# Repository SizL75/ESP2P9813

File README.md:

# ESP2P9813
PCB for ESP8266 ESP-01 board to control P9813 modules with 12v power supply

Can be used with fastled library, use the following settings:
```
#define DATA_PIN    2
#define CLK_PIN   0
#define LED_TYPE    P9813
#define COLOR_ORDER GRB
```

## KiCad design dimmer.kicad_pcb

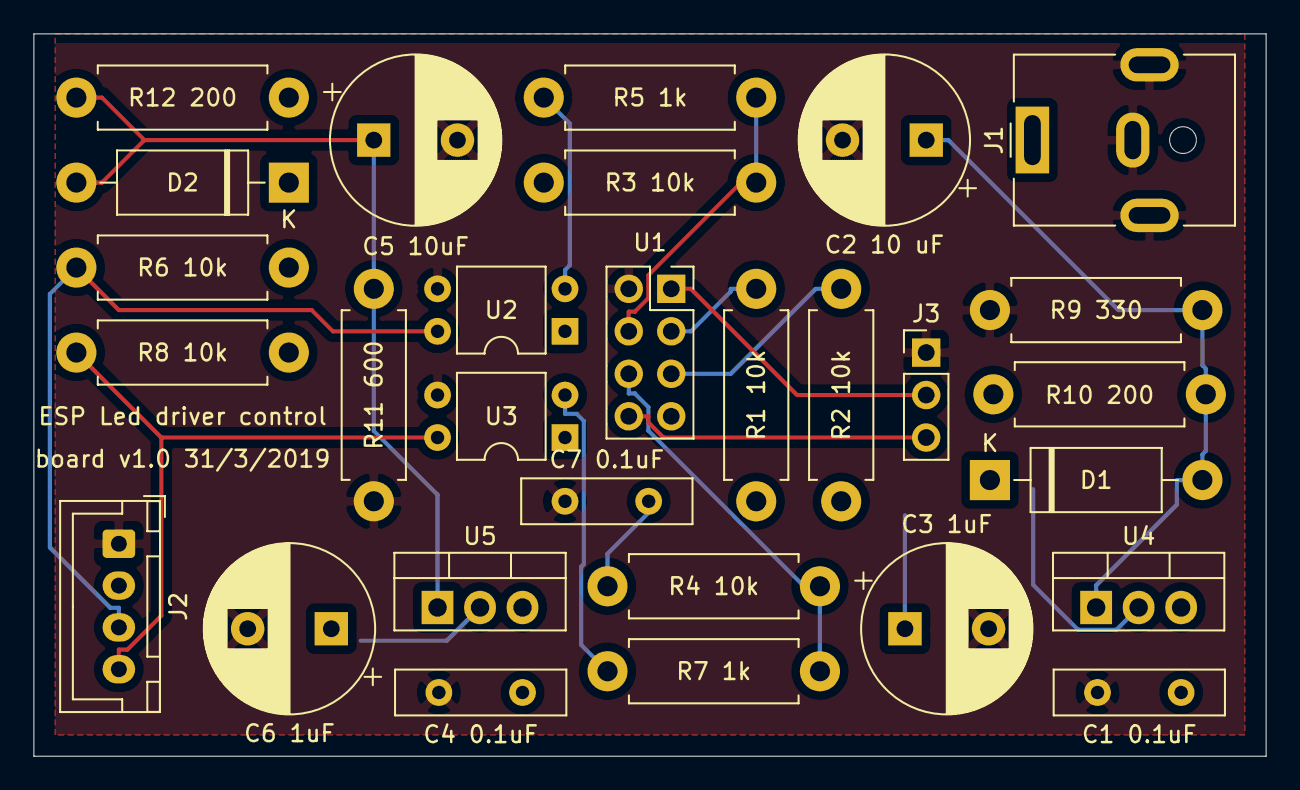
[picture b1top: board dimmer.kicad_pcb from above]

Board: 2 copper layers, 73.7 x 43.2 mm, 29 parts (0 on the bottom side), 16 nets.

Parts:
C1 0.1uF, C4 0.1uF, C7 0.1uF: 0.1uF; C_Disc_D10.0mm_W2.5mm_P5.00mm
C2 10 uF, C5 10uF: 10uF; CP_Radial_D10.0mm_P5.00mm
C3 1uF, C6 1uF: 1uF; CP_Radial_D10.0mm_P5.00mm
D1, D2: D; D_DO-15_P12.70mm_Horizontal
J1: Barrel_Jack_MountingPin; BarrelJack_CUI_PJ-063AH_Horizontal
J2: Conn_01x04_Male; JST_XH_B4B-XH-A_1x04_P2.50mm_Vertical
J3: Conn_01x03_Male; PinHeader_1x03_P2.54mm_Vertical
R1 10k, R2 10k, R3 10k, R4 10k, R6 10k, R8 10k: 10k; R_Axial_DIN0411_L9.9mm_D3.6mm_P12.70mm_Horizontal
R5 1k, R7 1k: 1k; R_Axial_DIN0411_L9.9mm_D3.6mm_P12.70mm_Horizontal
R9 330: 330; R_Axial_DIN0411_L9.9mm_D3.6mm_P12.70mm_Horizontal
R10 200, R12 200: 200; R_Axial_DIN0411_L9.9mm_D3.6mm_P12.70mm_Horizontal
R11 600: 600; R_Axial_DIN0411_L9.9mm_D3.6mm_P12.70mm_Horizontal
U1: ESP-01v090; PinSocket_2x04_P2.54mm_Vertical
U2, U3: LTV-817; DIP-4_W7.62mm
U4, U5: LM317; TO-220-3_Vertical

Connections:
+3V3: C3 1uF.1, C7 0.1uF.2, D1.1, R1 10k.1, R2 10k.1, R3 10k.2, R4 10k.2, R10 200.1, U1.7, U2.1, U3.1, U4.2
+5V: C6 1uF.1, D2.1, J2.2, R6 10k.2, R8 10k.2, R12 200.1, U5.2
+12V: C1 0.1uF.1, C4 0.1uF.1, J1.1, U4.3, U5.3
Clock: R4 10k.1, R7 1k.2, U1.6
Clock_out: J2.4, R8 10k.1, U3.4
Data: R3 10k.1, R5 1k.2, U1.4
Data_out: J2.3, R6 10k.1, U2.4
GND: C1 0.1uF.2, C2 10 uF.2, C3 1uF.2, C4 0.1uF.2, C5 10uF.2, C6 1uF.2, C7 0.1uF.1, J1.2, J1.MP, J2.1, J3.1, R9 330.2, R11 600.2, U1.2, U2.3, U3.3
unnamed: C2 10 uF.1, D1.2, R9 330.1, R10 200.2, U4.1
unnamed: C5 10uF.1, D2.2, R11 600.1, R12 200.2, U5.1
unnamed: R1 10k.2, U1.3
unnamed: R2 10k.2, U1.5
unnamed: R5 1k.1, U2.2
unnamed: R7 1k.1, U3.2
Rx: J3.3, U1.8
Tx: J3.2, U1.1

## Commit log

2019-03-31 Add files via upload
    PCB Schematic and board design
